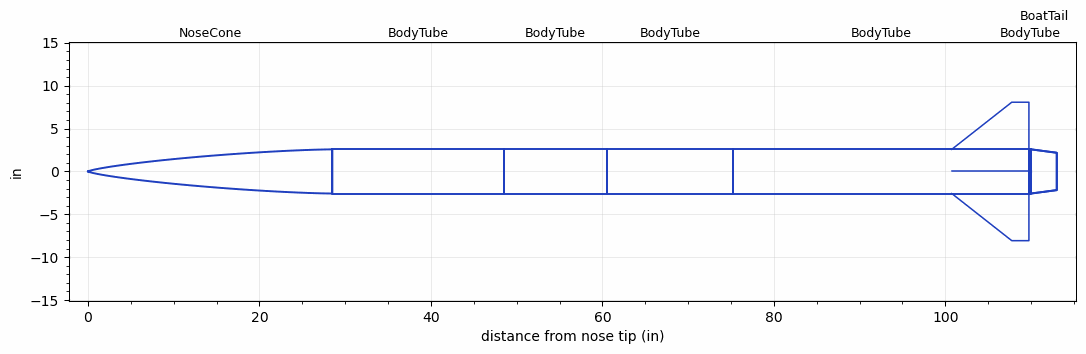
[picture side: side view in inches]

<RASAeroDocument>
 <FileVersion>2</FileVersion>
 <RocketDesign>
  <NoseCone>
   <Length>28.5</Length>
   <Diameter>5.15</Diameter>
   <Shape>Von Karman Ogive</Shape>
   <Location>0</Location>
  </NoseCone>
  <BodyTube>
   <Length>20</Length>
   <Diameter>5.15</Diameter>
   <Location>28.5</Location>
  </BodyTube>
  <BodyTube>
   <Length>12</Length>
   <Diameter>5.15</Diameter>
   <Location>48.5</Location>
  </BodyTube>
  <BodyTube>
   <Length>14.75</Length>
   <Diameter>5.15</Diameter>
   <Location>60.5</Location>
  </BodyTube>
  <BodyTube>
   <Length>34.5</Length>
   <Diameter>5.15</Diameter>
   <Location>75.25</Location>
   <BoattailOffset>0.25</BoattailOffset>
   <Fin>
    <Count>4</Count>
    <Chord>9</Chord>
    <Span>5.5</Span>
    <SweepDistance>7</SweepDistance>
    <TipChord>2</TipChord>
    <Thickness>0.2</Thickness>
    <LERadius>0.001</LERadius>
    <Location>9</Location>
    <AirfoilSection>Square</AirfoilSection>
    <FX1>0.5</FX1>
    <FX3>0.5</FX3>
   </Fin>
  </BodyTube>
  <BodyTube>
   <Length>0.25</Length>
   <Diameter>5.15</Diameter>
   <Location>109.75</Location>
   <BoattailLength>3</BoattailLength>
   <BoattailRearDiameter>4.36</BoattailRearDiameter>
  </BodyTube>
  <BoatTail>
   <Length>3</Length>
   <Diameter>5.15</Diameter>
   <RearDiameter>4.36</RearDiameter>
   <Location>110</Location>
  </BoatTail>
  <Surface>Smooth Paint</Surface>
  <ModifiedBarrowman>False</ModifiedBarrowman>
  <Turbulence>False</Turbulence>
  <SustainerNozzle>2.7</SustainerNozzle>
  <UseBooster1>False</UseBooster1>
  <UseBooster2>False</UseBooster2>
 </RocketDesign>
 <LaunchSite>
  <Altitude>950</Altitude>
  <Pressure>30</Pressure>
  <RodAngle>1</RodAngle>
  <RodLength>16.25</RodLength>
  <Temperature>68</Temperature>
  <WindSpeed>5</WindSpeed>
 </LaunchSite>
 <Recovery>
  <Altitude1>1000</Altitude1>
  <Altitude2>1500</Altitude2>
  <DeviceType1>Parachute</DeviceType1>
  <DeviceType2>Parachute</DeviceType2>
  <Event1>True</Event1>
  <Event2>True</Event2>
  <Size1>24</Size1>
  <Size2>72</Size2>
  <EventType1>Apogee</EventType1>
  <EventType2>Altitude</EventType2>
  <CD1>1.55</CD1>
  <CD2>2.2</CD2>
 </Recovery>
 <SimulationList>
  <Simulation>
   <SustainerEngine>M3400-WT  (CTI)</SustainerEngine>
   <SustainerLaunchWt>51.67</SustainerLaunchWt>
   <SustainerNozzleDiameter>2.7</SustainerNozzleDiameter>
   <SustainerCG>65.8</SustainerCG>
   <SustainerIgnitionDelay>0</SustainerIgnitionDelay>
   <Booster1SeparationDelay>0</Booster1SeparationDelay>
   <Booster1IgnitionDelay>0</Booster1IgnitionDelay>
   <IncludeBooster1>False</IncludeBooster1>
   <Booster2Delay>0</Booster2Delay>
   <IncludeBooster2>False</IncludeBooster2>
   <TimetoApogee>27.14053</TimetoApogee>
   <MaxAltitude>13765.03</MaxAltitude>
   <MaxVelocity>1337.525</MaxVelocity>
   <OptimumWt>27.77262</OptimumWt>
   <OptimumMaxAlt>27.77262</OptimumMaxAlt>
  </Simulation>
 </SimulationList>
</RASAeroDocument>
